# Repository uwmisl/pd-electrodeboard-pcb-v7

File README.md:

MISl v7 Electrode Board
=======================

Designed for [50x75mm frame](https://github.com/uwmisl/pd-frame-50x75).

Fiducials used: 13, 14, and 15

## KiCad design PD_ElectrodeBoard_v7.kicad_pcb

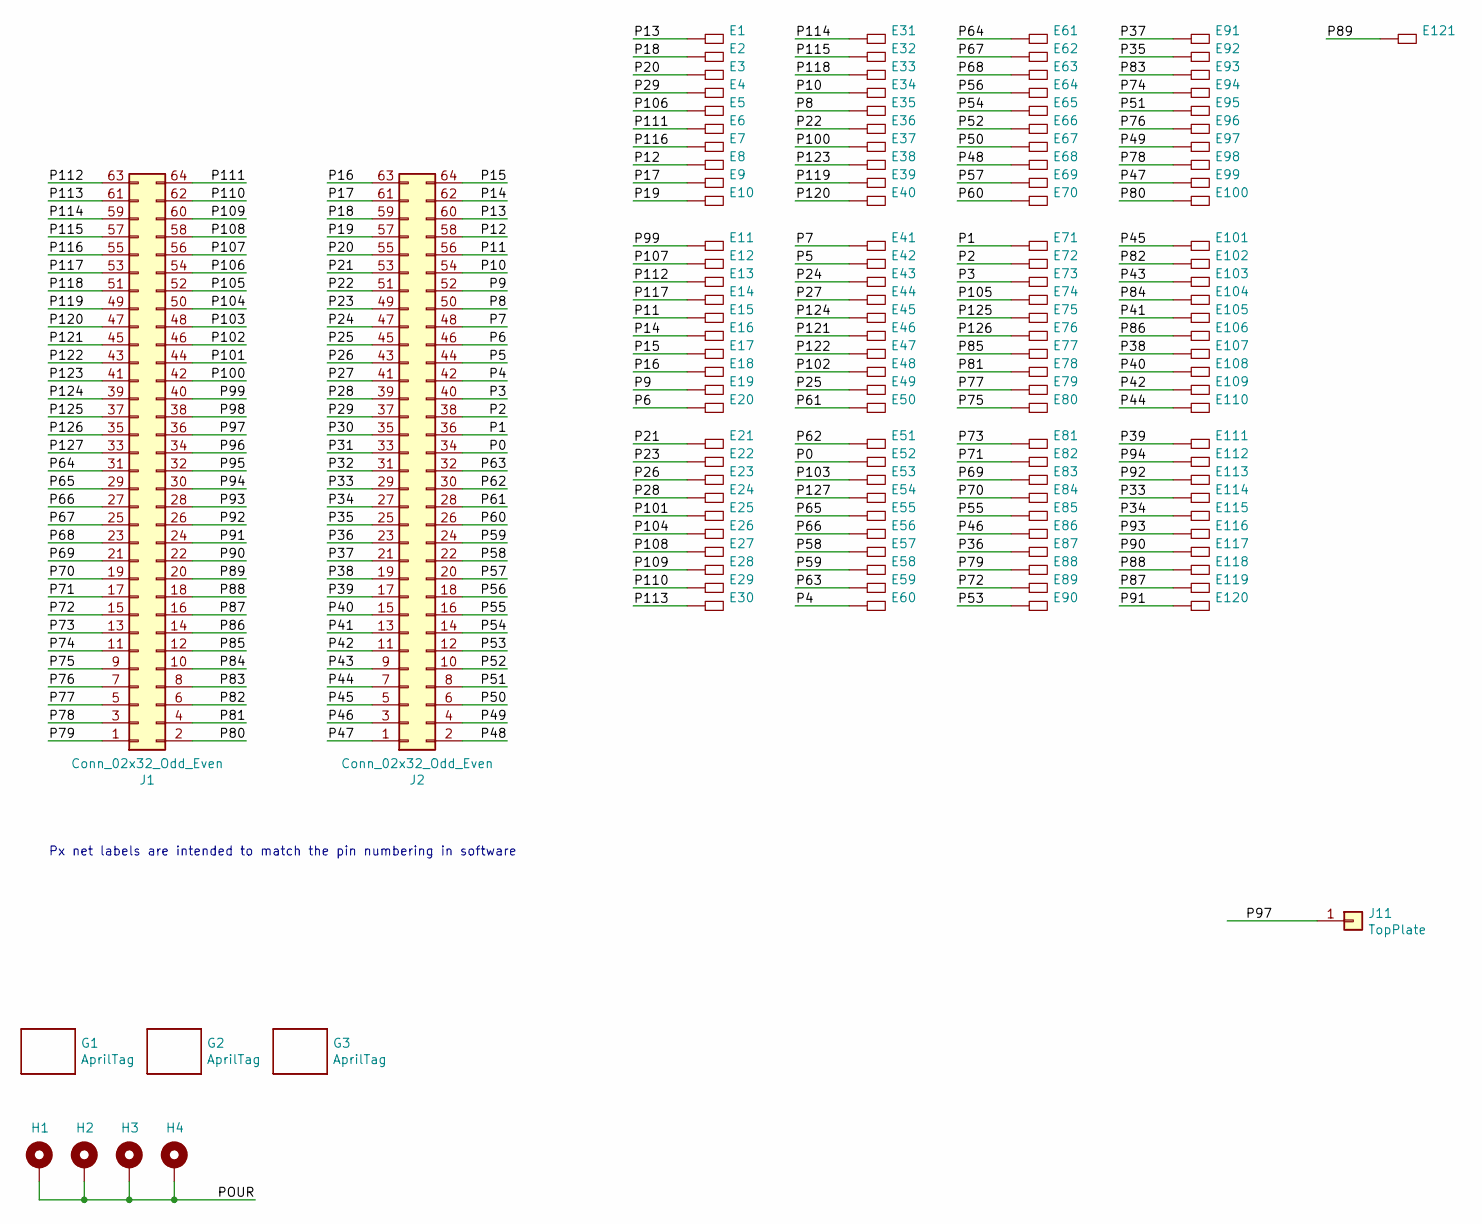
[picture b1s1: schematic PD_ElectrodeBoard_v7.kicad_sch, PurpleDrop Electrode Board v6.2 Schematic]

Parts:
E1, E2, E3, E4, E5, E6, E7, E8, E9, E10, E11, E12, E13, E14, E15, E16, E17, E18, E19, E20, E21, E22, E23, E24, E25, E26, E27, E28, E29, E30, E31, E32, E33, E34, E35, E36, E37, E38, E39, E40, E41, E42, E43, E44, E45, E46, E47, E48, E49, E50, E51, E52, E53, E54, E55, E56, E57, E58, E59, E60, E61, E62, E63, E64, E65, E66, E67, E68, E69, E70, E71, E72, E73, E74, E75, E76, E77, E78, E79, E80, E81, E82, E83, E84, E85, E86, E87, E88, E89, E90, E91, E92, E93, E94, E95, E96, E97, E98, E99, E100, E101, E102, E103, E104, E105, E106, E107, E108, E109, E110, E111, E112, E113, E114, E115, E116, E117, E118, E119, E120, E121: DMFElectrode; electrode_E1
G1: AprilTag; tag36_11_00013_7.00mm
G2: AprilTag; tag36_11_00014_7.00mm
G3: AprilTag; tag36_11_00015_7.00mm
H1, H2, H3, H4: MountingHole_Pad; Keystone-4929
J1, J2: Conn_02x32_Odd_Even; CLP-132-02-F-D
J11: TopPlate; Header1_RA

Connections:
/P0: E52.1, J2.34
/P1: E71.1, J2.36
/P2: E72.1, J2.38
/P3: E73.1, J2.40
/P4: E60.1, J2.42
/P5: E42.1, J2.44
/P6: E20.1, J2.46
/P7: E41.1, J2.48
/P8: E35.1, J2.50
/P9: E19.1, J2.52
/P10: E34.1, J2.54
/P11: E15.1, J2.56
/P12: E8.1, J2.58
/P13: E1.1, J2.60
/P14: E16.1, J2.62
/P15: E17.1, J2.64
/P16: E18.1, J2.63
/P17: E9.1, J2.61
/P18: E2.1, J2.59
/P19: E10.1, J2.57
/P20: E3.1, J2.55
/P21: E21.1, J2.53
/P22: E36.1, J2.51
/P23: E22.1, J2.49
/P24: E43.1, J2.47
/P25: E49.1, J2.45
/P26: E23.1, J2.43
/P27: E44.1, J2.41
/P28: E24.1, J2.39
/P29: E4.1, J2.37
/P30: J2.35
/P31: J2.33
/P32: J2.31
/P33: E114.1, J2.29
/P34: E115.1, J2.27
/P35: E92.1, J2.25
/P36: E87.1, J2.23
/P37: E91.1, J2.21
/P38: E107.1, J2.19
/P39: E111.1, J2.17
/P40: E108.1, J2.15
/P41: E105.1, J2.13
/P42: E109.1, J2.11
/P43: E103.1, J2.9
/P44: E110.1, J2.7
/P45: E101.1, J2.5
/P46: E86.1, J2.3
/P47: E99.1, J2.1
/P48: E68.1, J2.2
/P49: E97.1, J2.4
/P50: E67.1, J2.6
/P51: E95.1, J2.8
/P52: E66.1, J2.10
/P53: E90.1, J2.12
/P54: E65.1, J2.14
/P55: E85.1, J2.16
/P56: E64.1, J2.18
/P57: E69.1, J2.20
/P58: E57.1, J2.22
/P59: E58.1, J2.24
/P60: E70.1, J2.26
/P61: E50.1, J2.28
/P62: E51.1, J2.30
/P63: E59.1, J2.32
/P64: E61.1, J1.31
/P65: E55.1, J1.29
/P66: E56.1, J1.27
/P67: E62.1, J1.25
/P68: E63.1, J1.23
/P69: E83.1, J1.21
/P70: E84.1, J1.19
/P71: E82.1, J1.17
/P72: E89.1, J1.15
/P73: E81.1, J1.13
/P74: E94.1, J1.11
/P75: E80.1, J1.9
/P76: E96.1, J1.7
/P77: E79.1, J1.5
/P78: E98.1, J1.3
/P79: E88.1, J1.1
/P80: E100.1, J1.2
/P81: E78.1, J1.4
/P82: E102.1, J1.6
/P83: E93.1, J1.8
/P84: E104.1, J1.10
/P85: E77.1, J1.12
/P86: E106.1, J1.14
/P87: E119.1, J1.16
/P88: E118.1, J1.18
/P89: E121.1, J1.20
/P90: E117.1, J1.22
/P91: E120.1, J1.24
/P92: E113.1, J1.26
/P93: E116.1, J1.28
/P94: E112.1, J1.30
/P95: J1.32
/P96: J1.34
/P97: J1.36, J11.1
/P98: J1.38
/P99: E11.1, J1.40
/P100: E37.1, J1.42
/P101: E25.1, J1.44
/P102: E48.1, J1.46
/P103: E53.1, J1.48
/P104: E26.1, J1.50
/P105: E74.1, J1.52
/P106: E5.1, J1.54
/P107: E12.1, J1.56
/P108: E27.1, J1.58
/P109: E28.1, J1.60
/P110: E29.1, J1.62
/P111: E6.1, J1.64
/P112: E13.1, J1.63
/P113: E30.1, J1.61
/P114: E31.1, J1.59
/P115: E32.1, J1.57
/P116: E7.1, J1.55
/P117: E14.1, J1.53
/P118: E33.1, J1.51
/P119: E39.1, J1.49
/P120: E40.1, J1.47
/P121: E46.1, J1.45
/P122: E47.1, J1.43
/P123: E38.1, J1.41
/P124: E45.1, J1.39
/P125: E75.1, J1.37
/P126: E76.1, J1.35
/P127: E54.1, J1.33
/POUR: H1.1, H2.1, H3.1, H4.1

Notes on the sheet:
Px net labels are intended to match the pin numbering in software

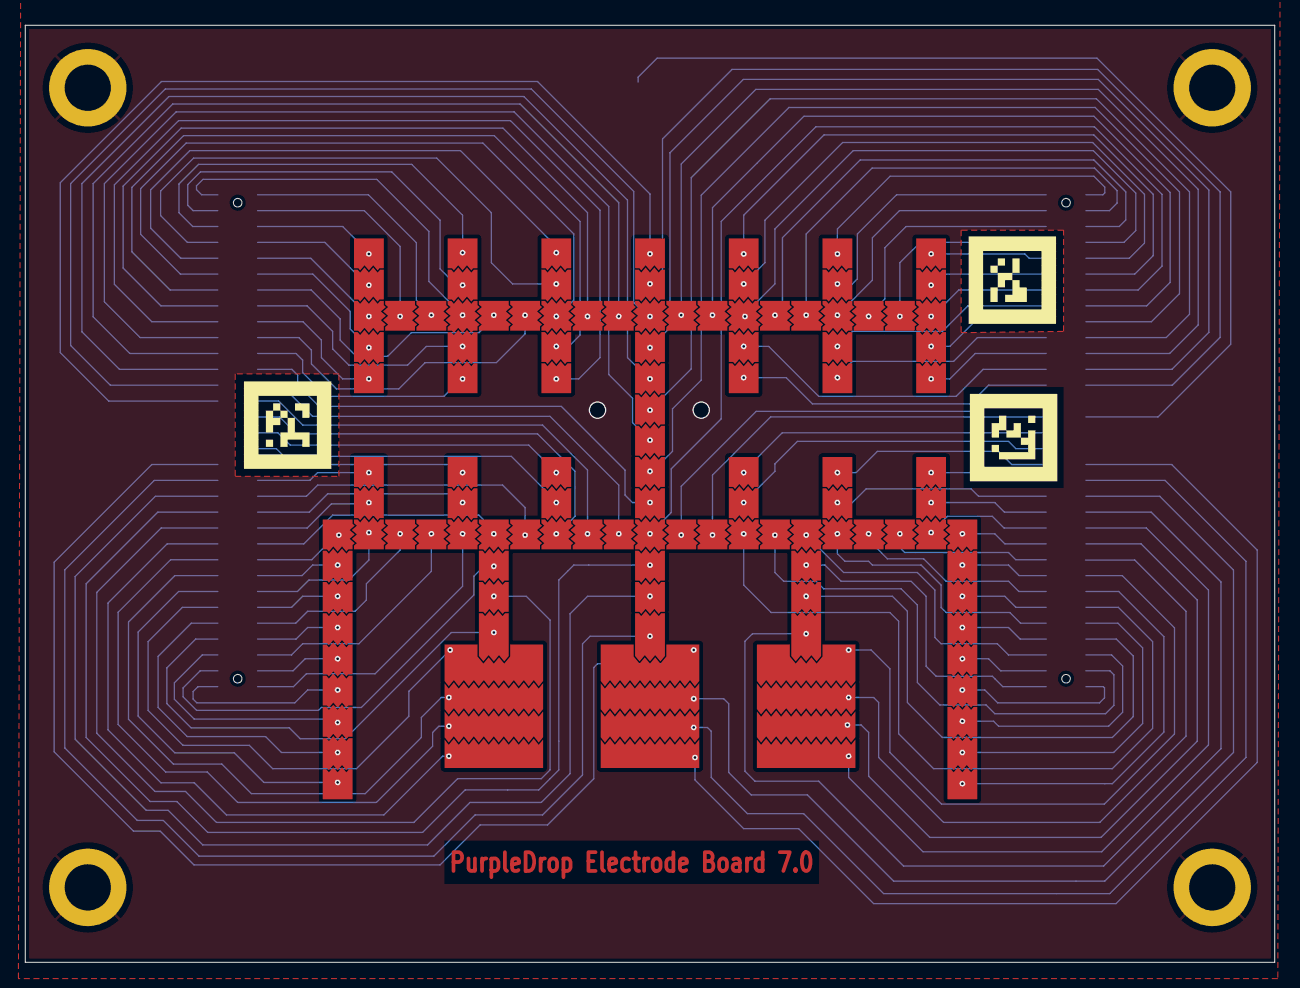
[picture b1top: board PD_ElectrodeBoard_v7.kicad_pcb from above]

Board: 2 copper layers, 100.0 x 75.0 mm, 131 parts (1 on the bottom side), 123 nets.

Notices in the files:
parts and their libraries:
Copyright 2016 Accelerated Designs. All rights reserved.
